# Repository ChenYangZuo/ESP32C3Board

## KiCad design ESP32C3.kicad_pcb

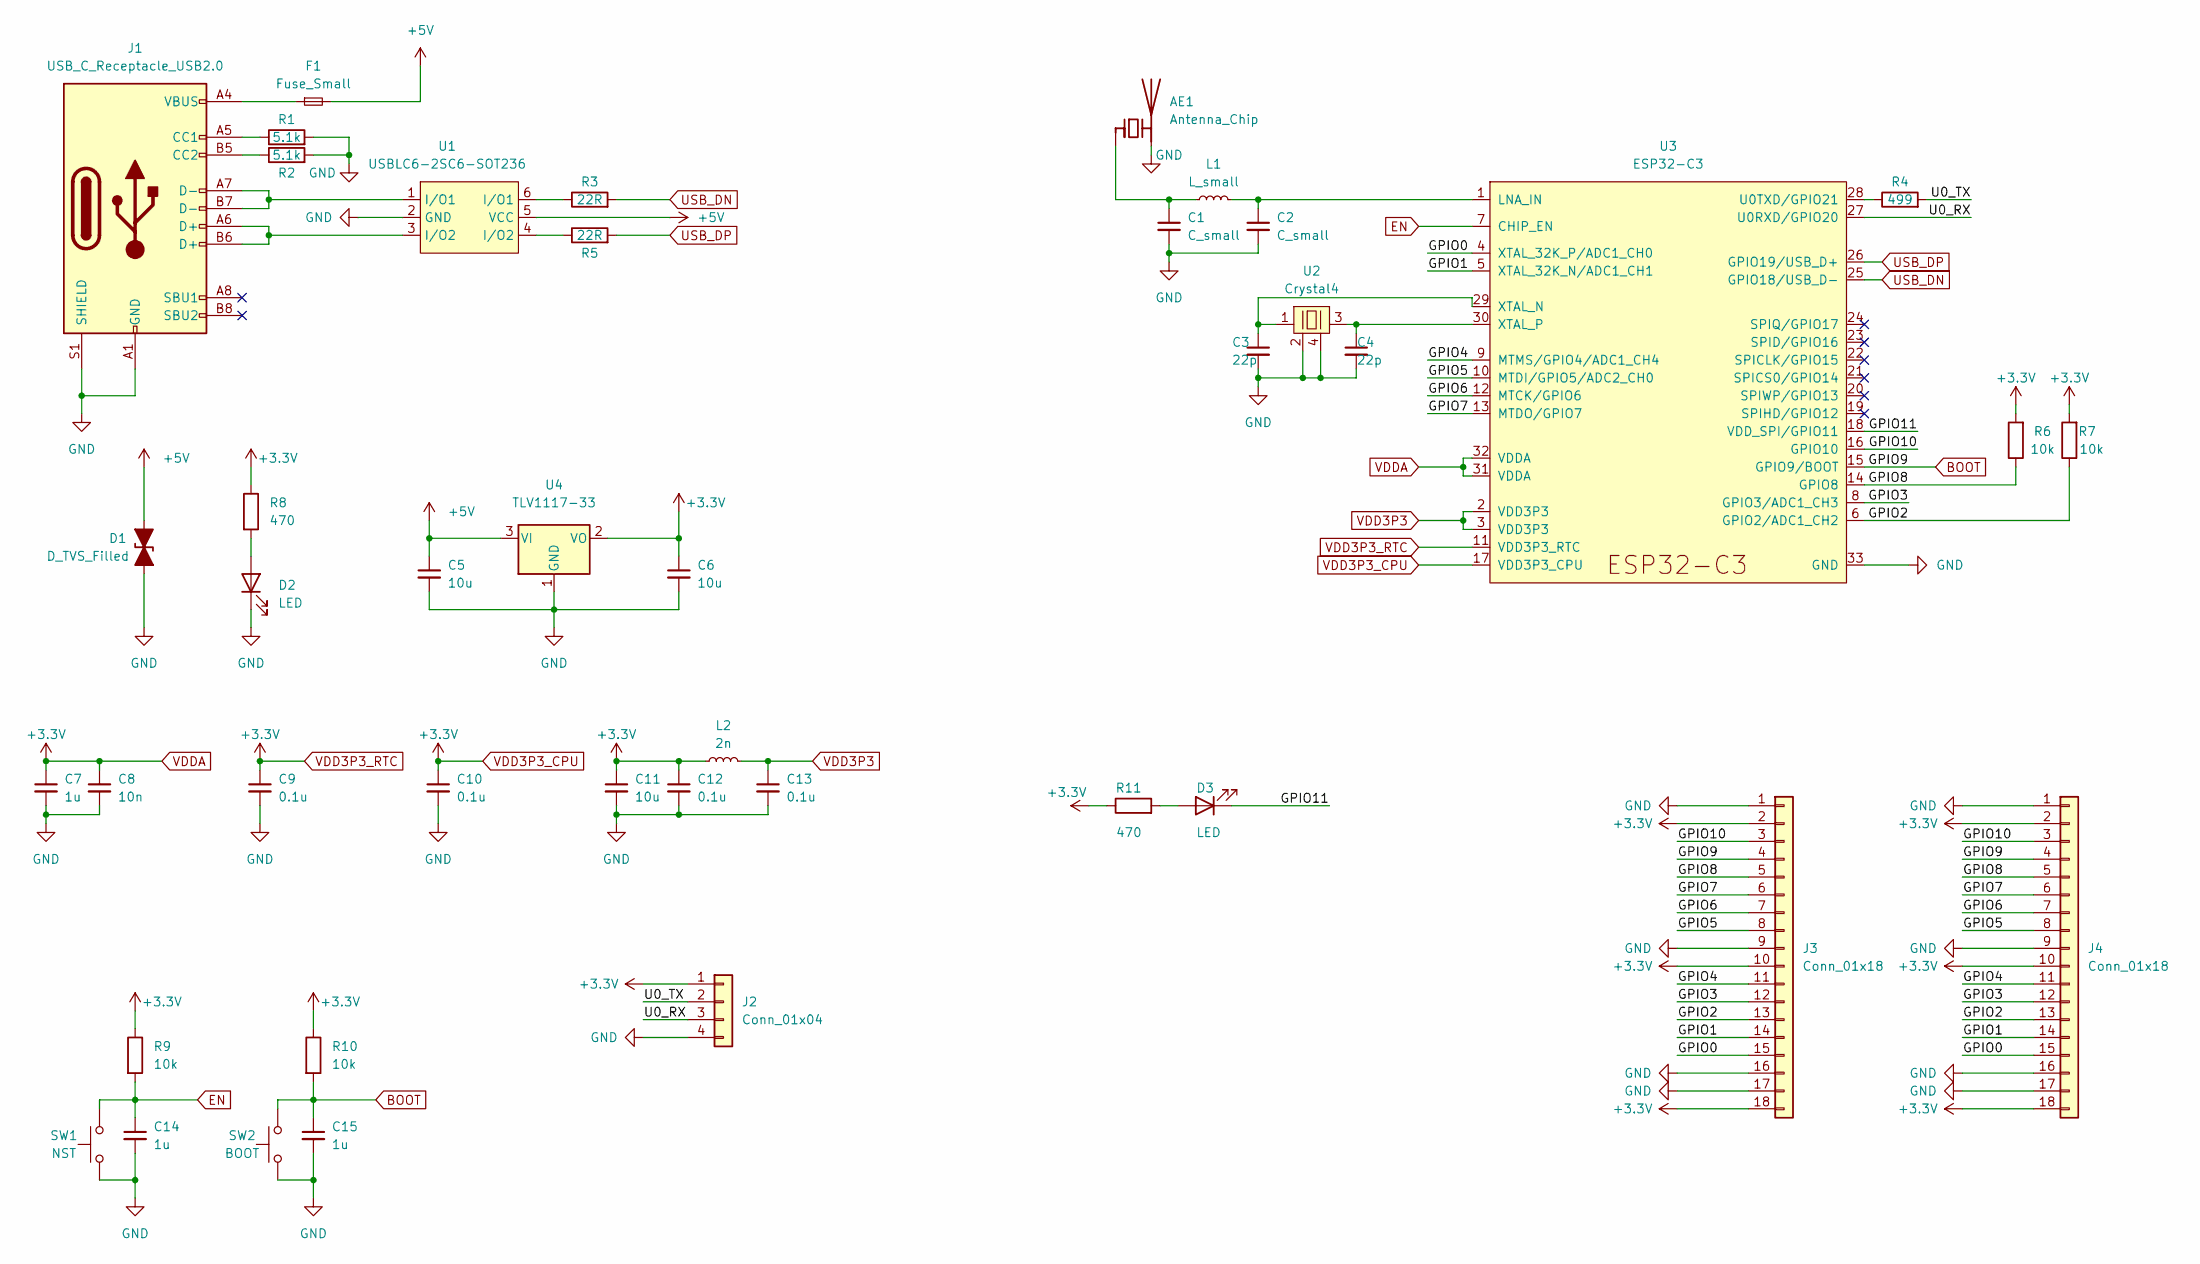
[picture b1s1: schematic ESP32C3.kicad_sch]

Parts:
AE1: Antenna_Chip; Texas_SWRA117D_2.4GHz_Right
C1, C2: C_small; C_0603_1608Metric
C3, C4: 22p; C_0603_1608Metric
C5, C6: 10u; C_0805_2012Metric
C7, C14, C15: 1u; C_0603_1608Metric
C8: 10n; C_0603_1608Metric
C9, C10, C12, C13: 0.1u; C_0603_1608Metric
C11: 10u; C_0603_1608Metric
D1: D_TVS_Filled; X1-DFN1006-2_L1.0-W0.6-BI
D2, D3: LED; LED_0603_1608Metric
F1: Fuse_Small; Fuse_1206_3216Metric
J1: USB_C_Receptacle_USB2.0; USB_C_Receptacle_XKB_U262-16XN-4BVC11
J2: Conn_01x04; Harwin_M20-89004xx_1x04_P2.54mm_Horizontal
J3: Conn_01x18; PinHeader_1x18_P2.54mm_Vertical
J4: Conn_01x18; PinSocket_1x18_P2.54mm_Vertical
L1: L_small; L_0603_1608Metric
L2: 2n; L_0805_2012Metric
R1, R2: 5.1k; R_0603_1608Metric
R3, R5: 22R; R_0603_1608Metric
R4: 499; R_0603_1608Metric
R6, R7, R9, R10: 10k; R_0603_1608Metric
R8, R11: 470; R_0603_1608Metric
SW1: NST; SW-SMD_L6.0-W3.3-LS8.0
SW2: BOOT; SW-SMD_L6.0-W3.3-LS8.0
U1: USBLC6-2SC6-SOT236; SOT-23-6
U2: Crystal4; Crystal_SMD_3225-4Pin_3.2x2.5mm
U3: ESP32-C3; QFN-32-1EP_5x5mm_P0.5mm_EP3.45x3.45mm
U4: TLV1117-33; SOT-223-3_TabPin2

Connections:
+5V: C5.1, D1.2 (A2), F1.2, U1.5 (VCC), U4.3 (VI)
/GPIO0: J3.15, J4.15, U3.4 (XTAL_32K_P/ADC1_CH0)
/GPIO1: J3.14, J4.14, U3.5 (XTAL_32K_N/ADC1_CH1)
/GPIO2: J3.13, J4.13, R7.1, U3.6 (GPIO2/ADC1_CH2)
/GPIO3: J3.12, J4.12, U3.8 (GPIO3/ADC1_CH3)
/GPIO4: J3.11, J4.11, U3.9 (MTMS/GPIO4/ADC1_CH4)
/GPIO5: J3.8, J4.8, U3.10 (MTDI/GPIO5/ADC2_CH0)
/GPIO6: J3.7, J4.7, U3.12 (MTCK/GPIO6)
/GPIO7: J3.6, J4.6, U3.13 (MTDO/GPIO7)
/GPIO8: J3.5, J4.5, R6.1, U3.14 (GPIO8)
/GPIO10: J3.3, J4.3, U3.16 (GPIO10)
/GPIO11: D3.1 (K), U3.18 (VDD_SPI/GPIO11)
/U0_RX: J2.3, U3.27 (U0RXD/GPIO20)
/U0_TX: J2.2, R4.2
BOOT: C15.1, J3.4, J4.4, R10.2, SW2.2, U3.15 (GPIO9/BOOT)
EN: C14.1, R9.2, SW1.2, U3.7 (CHIP_EN)
GND: AE1.2 (PCB_Trace), C1.2, C2.2, C3.2, C4.2, C5.2, C6.2, C7.2, C8.2, C9.2, C10.2, C11.2, C12.2, C13.2, C14.2, C15.2, D1.1 (A1), D2.1 (K), J1.A1 (GND), J1.A12 (GND), J1.B1 (GND), J1.B12 (GND), J1.S1 (SHIELD), J2.4, J3.1, J3.9, J3.16, J3.17, J4.1, J4.9, J4.16, J4.17, R1.2, R2.2, SW1.1, SW2.1, U1.2 (GND), U2.2, U2.4, U3.33 (GND), U4.1 (GND)
unnamed: AE1.1 (FEED), C1.1, L1.1
unnamed: C2.1, L1.2, U3.1 (LNA_IN)
unnamed: C3.1, U2.1, U3.29 (XTAL_N)
unnamed: C4.1, U2.3, U3.30 (XTAL_P)
unnamed: D2.2 (A), R8.2
unnamed: D3.2 (A), R11.2
unnamed: F1.1, J1.A4 (VBUS), J1.A9 (VBUS), J1.B4 (VBUS), J1.B9 (VBUS)
unnamed: J1.A5 (CC1), R1.1
unnamed: J1.A6 (D+), J1.B6 (D+), U1.3 (I/O2)
unnamed: J1.A7 (D-), J1.B7 (D-), U1.1 (I/O1)
unnamed: J1.B5 (CC2), R2.1
unnamed: R3.1, U1.6 (I/O1)
unnamed: R4.1, U3.28 (U0TXD/GPIO21)
unnamed: R5.1, U1.4 (I/O2)
USB_DN: R3.2, U3.25 (GPIO18/USB_D-)
USB_DP: R5.2, U3.26 (GPIO19/USB_D+)
VDD3P3: C13.1, L2.2, U3.2 (VDD3P3), U3.3 (VDD3P3)
VDD3P3_CPU: C6.1, C7.1, C8.1, C9.1, C10.1, C11.1, C12.1, J2.1, J3.2, J3.10, J3.18, J4.2, J4.10, J4.18, L2.1, R6.2, R7.2, R8.1, R9.1, R10.1, R11.1, U3.11 (VDD3P3_RTC), U3.17 (VDD3P3_CPU), U3.31 (VDDA), U3.32 (VDDA), U4.2 (VO)

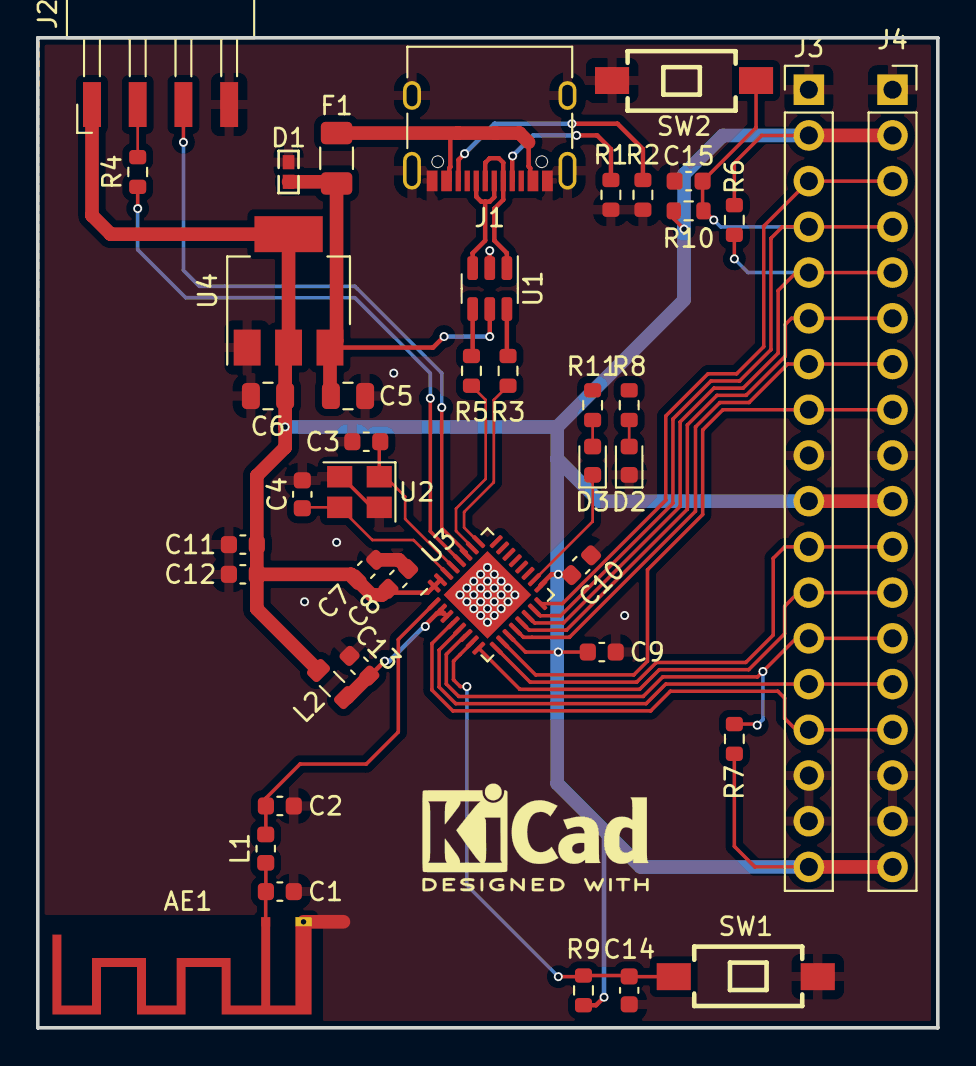
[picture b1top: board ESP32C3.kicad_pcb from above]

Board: 2 copper layers, 50.0 x 55.0 mm, 43 parts (0 on the bottom side), 35 nets.

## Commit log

2022-06-26 First commit.
2022-07-06 Made some changes.
2022-07-07 Changes.
2022-07-07 maybe finish.
2022-07-09 add gerber.
